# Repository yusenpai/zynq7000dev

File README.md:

# Zynq 7000 SoC Dev Board

Đây là một board PCB 6 lớp thiết kế quanh con chip XC7Z010-1CLG400C, thuộc họ SoC Zynq 7000 của AMD. Con chip có một nửa là (2) lõi CPU (ARM Cortex-A9) + một đống ngoại vi (UART, I2C, SPI, USB,...); nửa còn lại là FPGA. Rất phù hợp cho những ứng dụng kết hợp Hardware + Software.

Thường thì những board FPGA (đặc biệt là thể loại SoC thế này) rất mắc tiền. Xem [https://www.amd.com/en/products/adaptive-socs-and-fpgas/evaluation-boards/ek-z7-zc702-g.html]. Trong khi đó, mạch in khá là rẻ, chip thì mình cũng kiếm được trên Aliexpress (với đi freesample), nên mình quyết định làm một board thế này.

Schematic, PCB vẫn đang trong quá trình phát triển và có thể sai sót. Mình sẽ cập nhật thêm nếu mạch chạy được 😂.

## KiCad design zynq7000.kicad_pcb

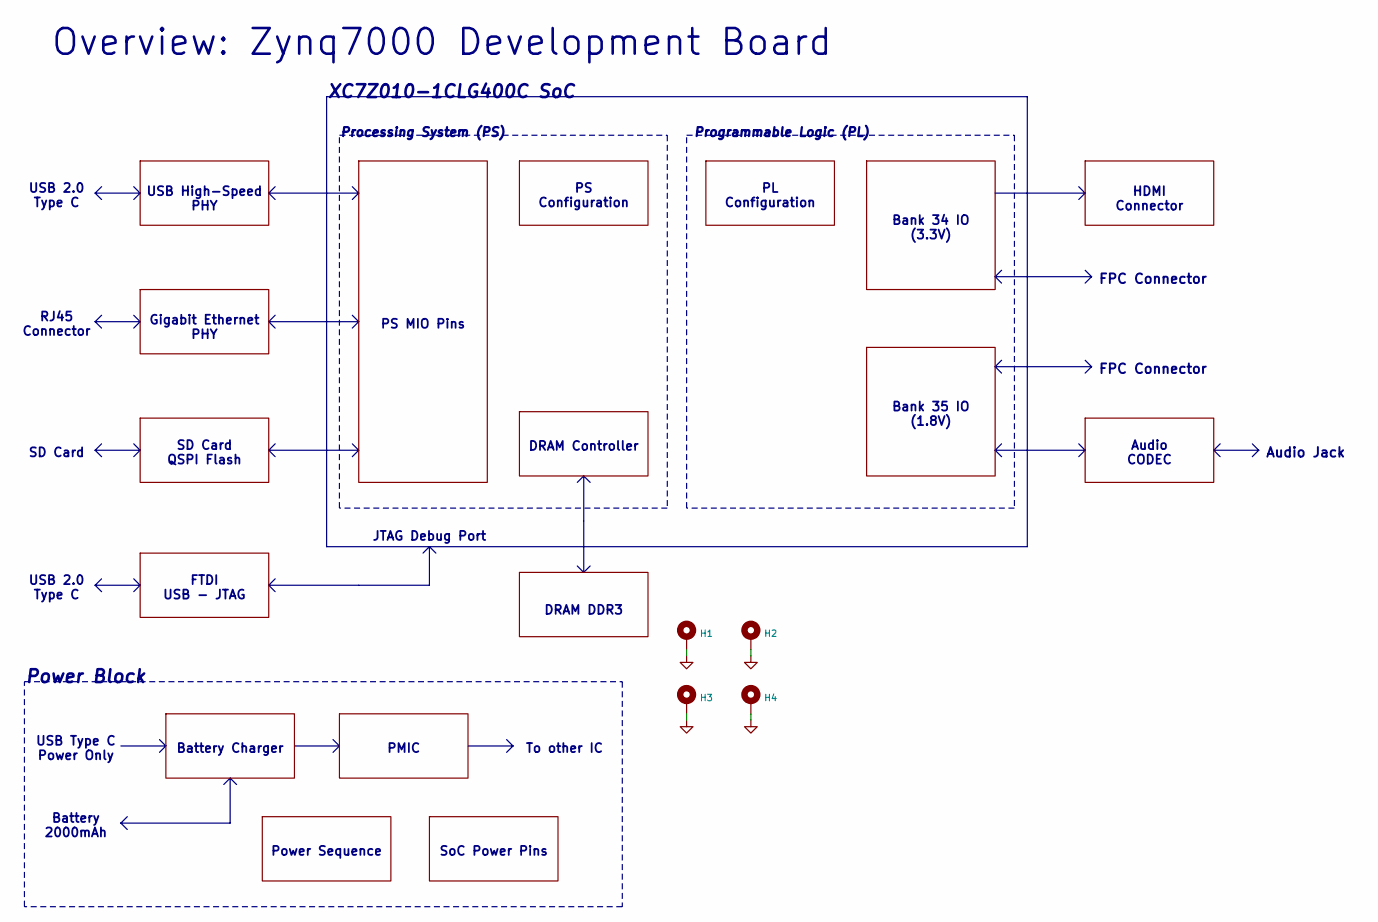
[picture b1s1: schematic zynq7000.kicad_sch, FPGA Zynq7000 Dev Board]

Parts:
H1, H2, H3, H4: MountingHole_Pad; MountingHole_3mm_Pad_Via

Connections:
GND: H1.1, H2.1, H3.1, H4.1; also elsewhere on the board

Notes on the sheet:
USB 2.0 Type C
Bank 34 IO (3.3V)
Processing System (PS)
FPC Connector
FTDI USB - JTAG
Audio Jack
PS Configuration
DRAM DDR3
Programmable Logic (PL)
Overview: Zynq7000 Development Board
To other IC
JTAG Debug Port
Power Block
SoC Power Pins
RJ45 Connector
USB Type C Power Only
PS MIO Pins
USB High-Speed PHY
Battery Charger
Gigabit Ethernet PHY
Power Sequence
HDMI Connector
Battery 2000mAh
PMIC
Audio CODEC
SD Card QSPI Flash
PL Configuration
Bank 35 IO (1.8V)
XC7Z010-1CLG400C SoC
DRAM Controller
SD Card

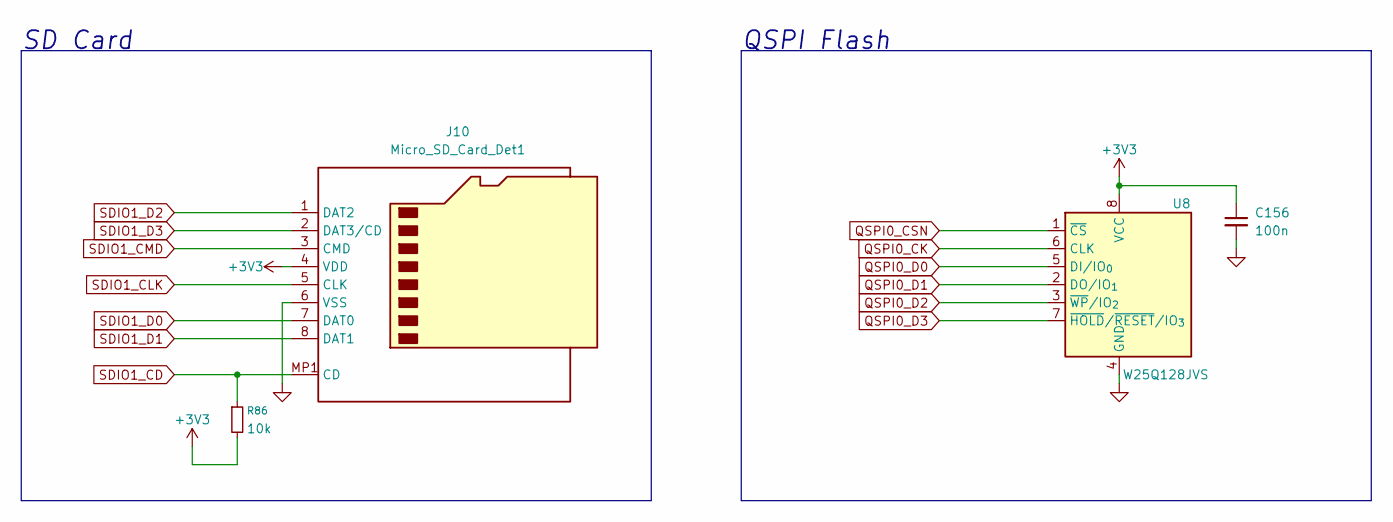
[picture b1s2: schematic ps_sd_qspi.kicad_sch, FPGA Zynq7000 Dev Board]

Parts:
C156: 100n; C_0402_1005Metric
J10: Micro_SD_Card_Det1; 5008730806
R86: 10k; R_0402_1005Metric
U8: W25Q128JVS; SOIC-8_5.3x5.3mm_P1.27mm

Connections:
+3V3: C156.1, J10.4 (VDD), R86.2, U8.8 (VCC); also elsewhere on the board
GND: C156.2, J10.6 (VSS), U8.4 (GND); also elsewhere on the board
QSPI0_CK: U8.6 (CLK); also elsewhere on the board
QSPI0_CSN: U8.1 (~CS); also elsewhere on the board
QSPI0_D0: U8.5 (DI/IO_{0}); also elsewhere on the board
QSPI0_D1: U8.2 (DO/IO_{1}); also elsewhere on the board
QSPI0_D2: U8.3 (~WP/IO_{2}); also elsewhere on the board
QSPI0_D3: U8.7 (~HOLD/~RESET/IO_{3}); also elsewhere on the board
SDIO1_CD: J10.MP1 (CD), R86.1; also elsewhere on the board
SDIO1_CLK: J10.5 (CLK); also elsewhere on the board
SDIO1_CMD: J10.3 (CMD); also elsewhere on the board
SDIO1_D0: J10.7 (DAT0); also elsewhere on the board
SDIO1_D1: J10.8 (DAT1); also elsewhere on the board
SDIO1_D2: J10.1 (DAT2); also elsewhere on the board
SDIO1_D3: J10.2 (DAT3/CD); also elsewhere on the board

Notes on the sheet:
QSPI Flash
SD Card

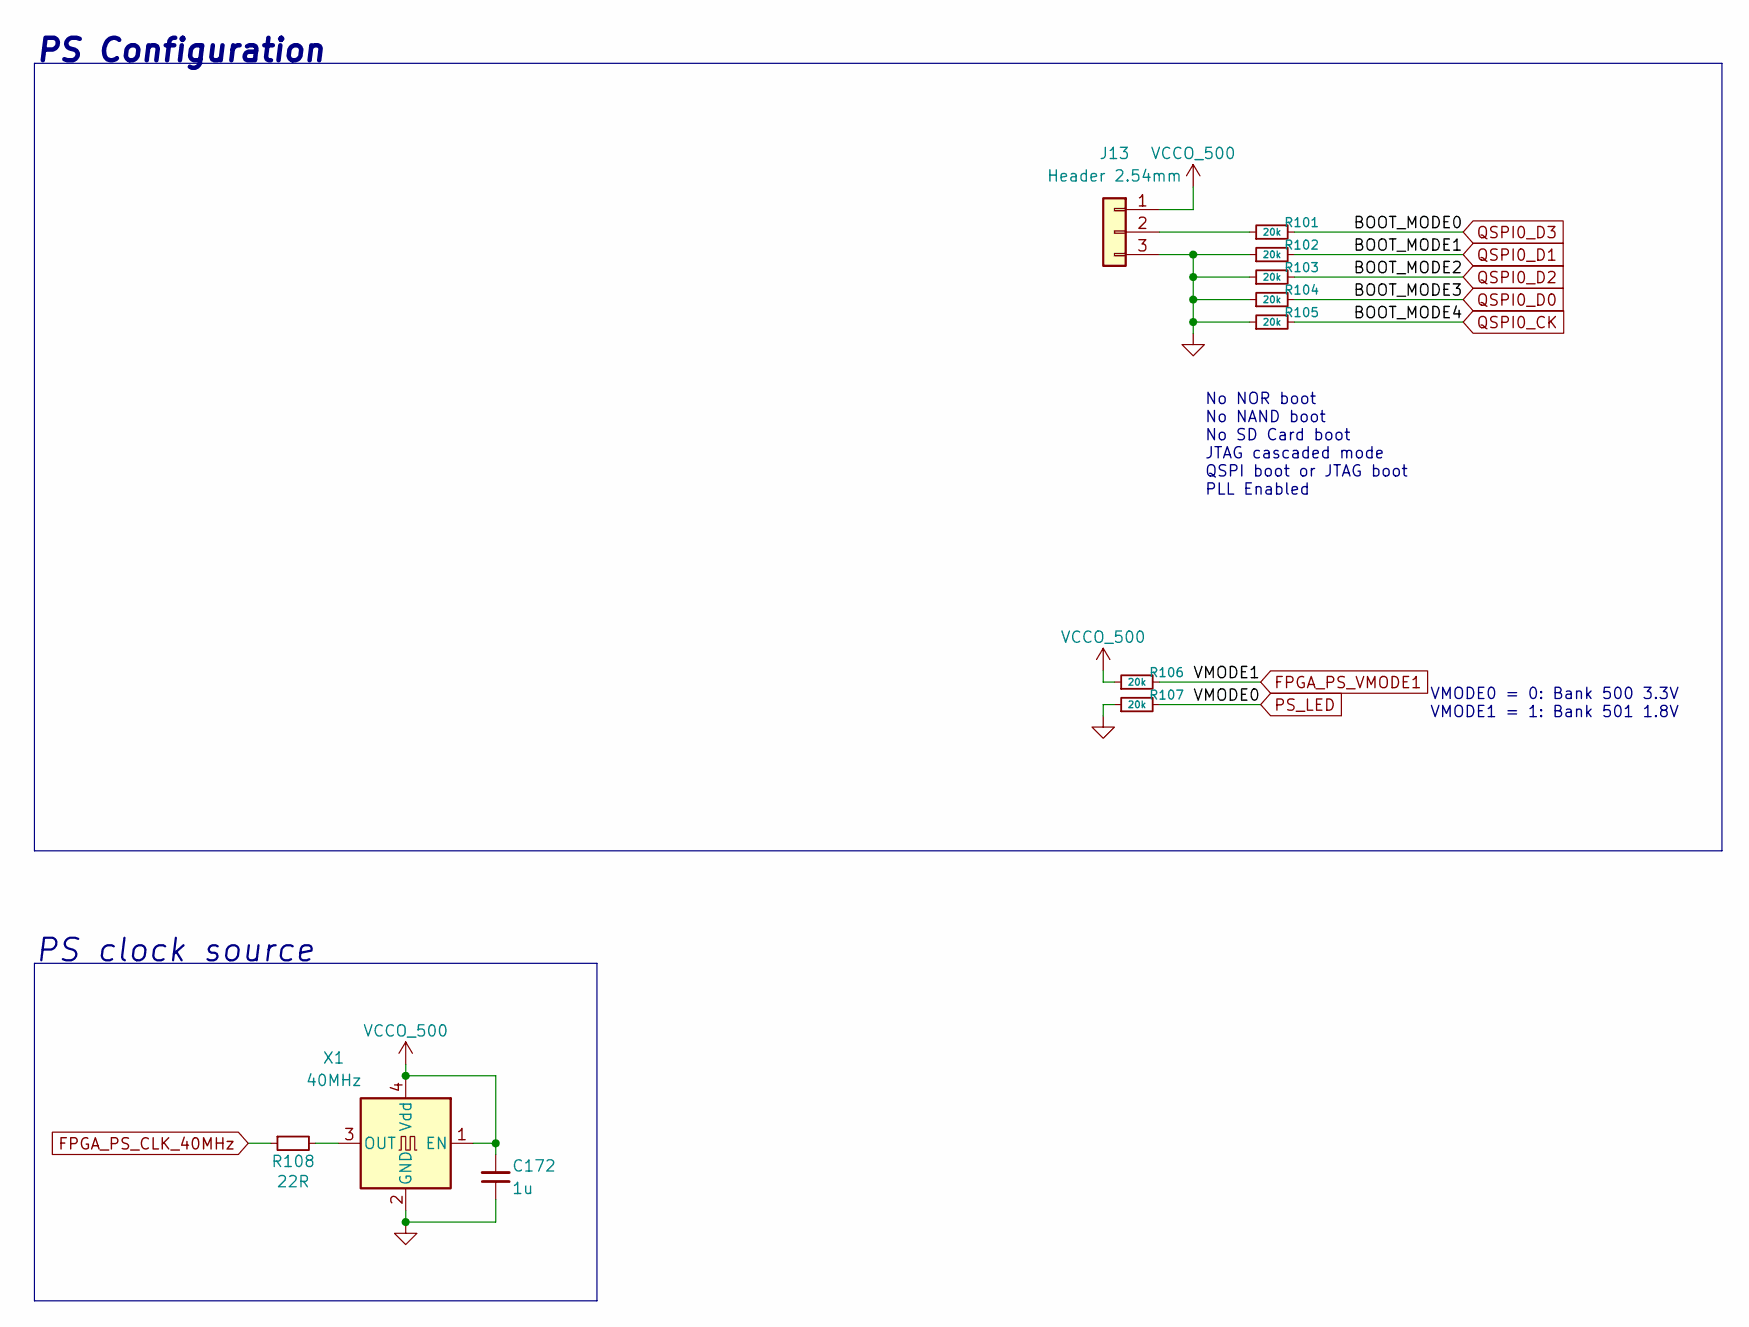
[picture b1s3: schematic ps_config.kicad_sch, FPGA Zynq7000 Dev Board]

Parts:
C172: 1u; C_0402_1005Metric
J13: Header 2.54mm; PinHeader_1x03_P2.54mm_Vertical
R101, R102, R103, R104, R105, R106, R107: 20k; R_0402_1005Metric
R108: 22R; R_0402_1005Metric
X1: 40MHz; Oscillator_SMD_Abracon_ASE-4Pin_3.2x2.5mm

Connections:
+3V3: C172.2, J13.1, R106.1, X1.1 (EN), X1.4 (Vdd); also elsewhere on the board
FPGA_PS_CLK_40MHz: R108.1; also elsewhere on the board
FPGA_PS_VMODE1: R106.2; also elsewhere on the board
GND: C172.1, J13.3, R102.1, R103.1, R104.1, R105.1, R107.1, X1.2 (GND); also elsewhere on the board
unnamed: J13.2, R101.1
unnamed: R108.2, X1.3 (OUT)
PS_LED: R107.2; also elsewhere on the board
QSPI0_CK: R105.2; also elsewhere on the board
QSPI0_D0: R104.2; also elsewhere on the board
QSPI0_D1: R102.2; also elsewhere on the board
QSPI0_D2: R103.2; also elsewhere on the board
QSPI0_D3: R101.2; also elsewhere on the board

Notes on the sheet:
PS clock source
VMODE0 = 0: Bank 500 3.3V VMODE1 = 1: Bank 501 1.8V
PS Configuration
No NOR boot No NAND boot No SD Card boot JTAG cascaded mode QSPI boot or JTAG boot PLL Enabled

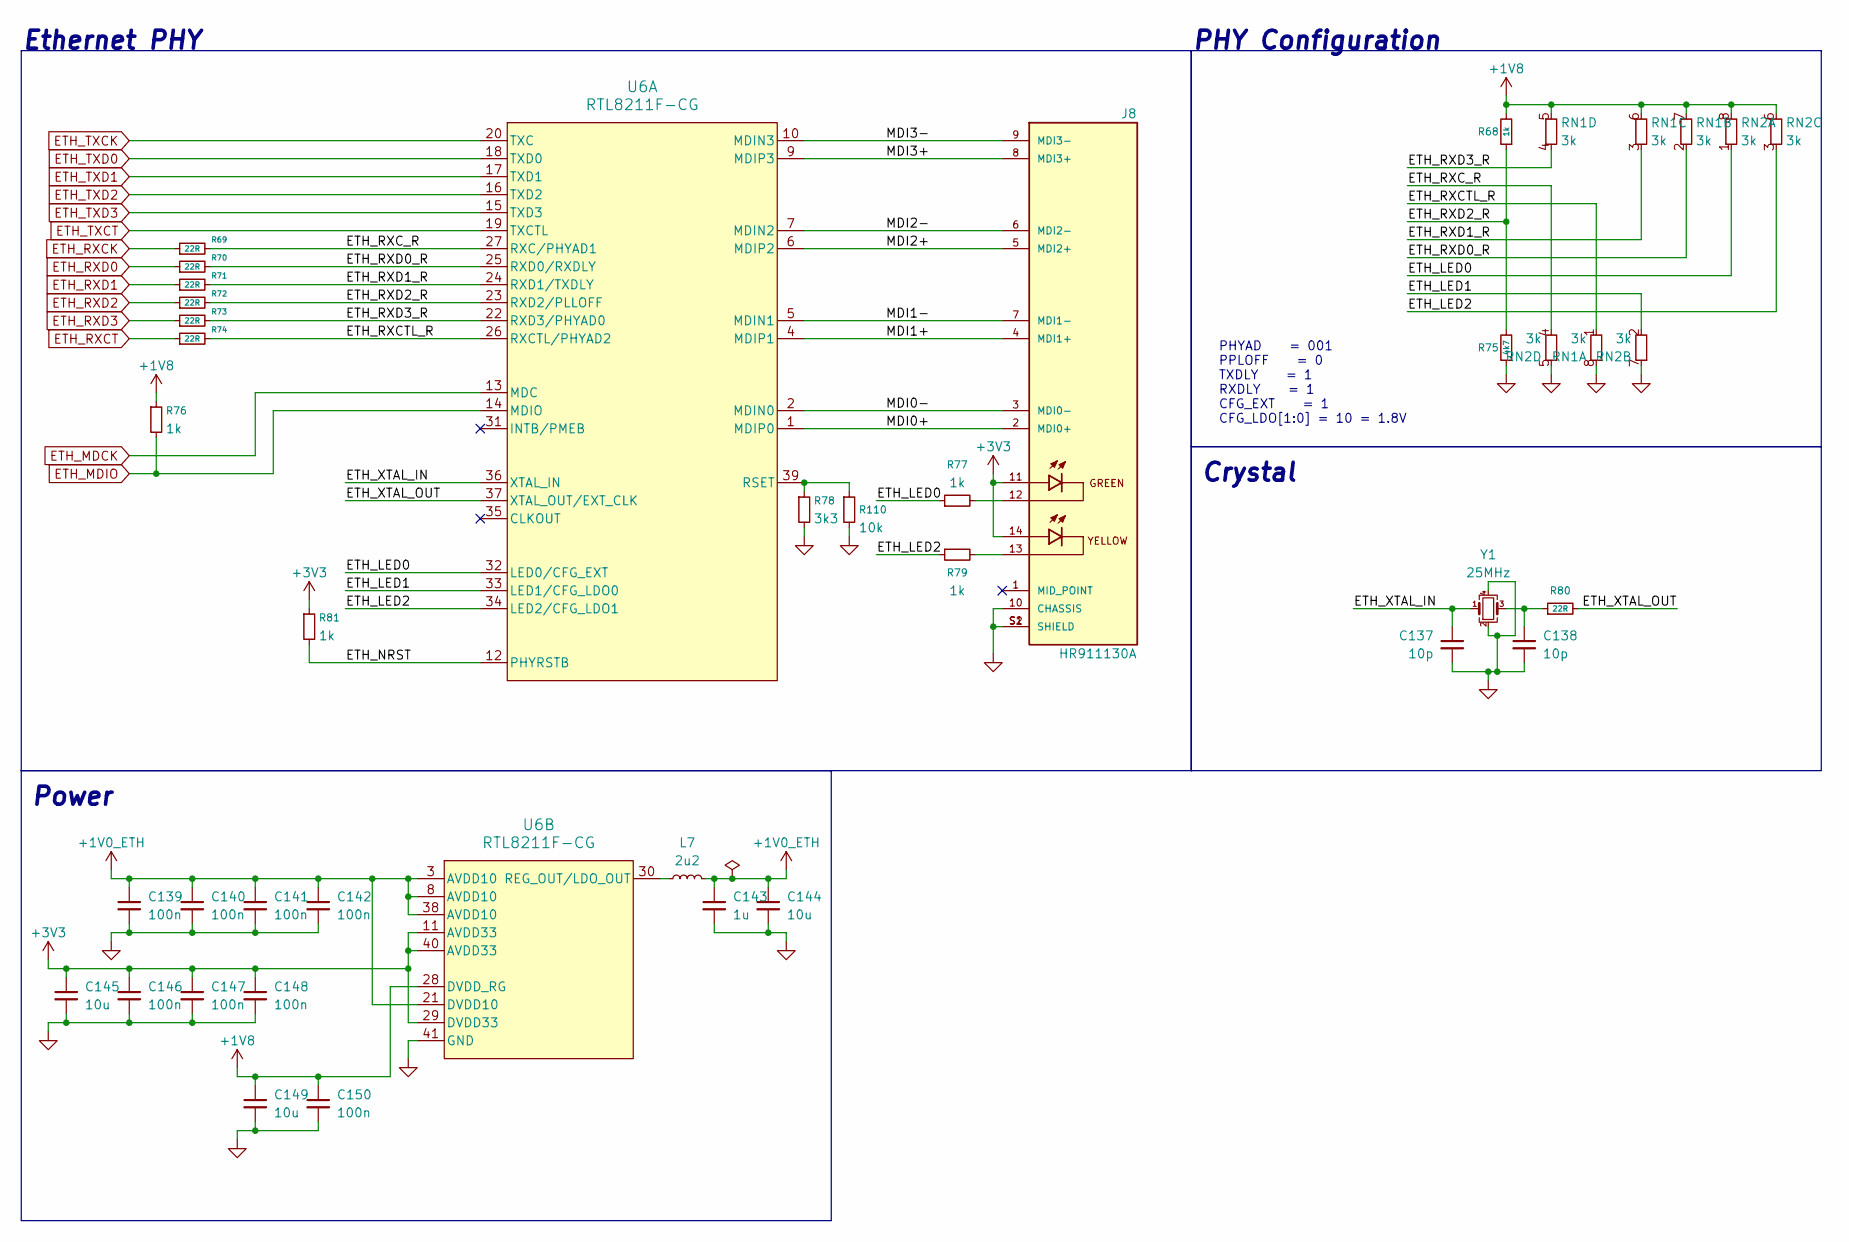
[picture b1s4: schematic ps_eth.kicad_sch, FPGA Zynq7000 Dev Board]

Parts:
C137, C138: 10p; C_0402_1005Metric
C139, C140, C141, C142, C146, C147, C148, C150: 100n; C_0402_1005Metric
C143: 1u; C_0402_1005Metric
C144, C145, C149: 10u; C_0402_1005Metric
J8: HR911130A; HANRUN_HR911130A; PARTREV A
L7: 2u2; L_1008_2520Metric
R68, R76, R77, R79, R81: 1k; R_0402_1005Metric
R69, R70, R71, R72, R73, R74, R80: 22R; R_0402_1005Metric
R75: 4k7; R_0402_1005Metric
R78: 3k3; R_0402_1005Metric
R110: 10k; R_0402_1005Metric
RN1, RN2: 3k; R_Array_Concave_4x0402
U6: RTL8211F-CG; QFN_40_7x7mm_RTL8211F
Y1: 25MHz; Crystal_SMD_3225-4Pin_3.2x2.5mm

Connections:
+1V0_ETH: C139.1, C140.1, C141.1, C142.1, C143.1, C144.1, L7.2, U6.3 (AVDD10), U6.8 (AVDD10), U6.21 (DVDD10), U6.38 (AVDD10)
+1V8: C149.1, C150.1, R68.2, R76.1, RN1.5 (R4.2), RN1.6 (R3.2), RN1.7 (R2.2), RN2.6 (R3.2), RN2.8, U6.28 (DVDD_RG); also elsewhere on the board
+3V3: C145.1, C146.1, C147.1, C148.1, J8.11, J8.14, R81.1, U6.11 (AVDD33), U6.29 (DVDD33), U6.40 (AVDD33); also elsewhere on the board
/Gigabit Ethernet PHY/ETH_LED0: R77.1, RN2.1, U6.32 (LED0/CFG_EXT)
/Gigabit Ethernet PHY/ETH_LED1: RN2.2 (R2.1), U6.33 (LED1/CFG_LDO0)
/Gigabit Ethernet PHY/ETH_LED2: R79.1, RN2.3 (R3.1), U6.34 (LED2/CFG_LDO1)
/Gigabit Ethernet PHY/ETH_NRST: R81.2, U6.12 (PHYRSTB)
/Gigabit Ethernet PHY/ETH_RXCTL_R: R74.2, RN1.1, U6.26 (RXCTL/PHYAD2)
/Gigabit Ethernet PHY/ETH_RXC_R: R69.2, RN2.4 (R4.1), U6.27 (RXC/PHYAD1)
/Gigabit Ethernet PHY/ETH_RXD0_R: R70.2, RN1.2 (R2.1), U6.25 (RXD0/RXDLY)
/Gigabit Ethernet PHY/ETH_RXD1_R: R71.2, RN1.3 (R3.1), U6.24 (RXD1/TXDLY)
/Gigabit Ethernet PHY/ETH_RXD2_R: R68.1, R72.2, R75.2, U6.23 (RXD2/PLLOFF)
/Gigabit Ethernet PHY/ETH_RXD3_R: R73.2, RN1.4 (R4.1), U6.22 (RXD3/PHYAD0)
/Gigabit Ethernet PHY/ETH_XTAL_IN: C137.1, U6.36 (XTAL_IN), Y1.1
/Gigabit Ethernet PHY/ETH_XTAL_OUT: R80.2, U6.37 (XTAL_OUT/EXT_CLK)
/Gigabit Ethernet PHY/MDI0+: J8.2 (MDI0+), U6.1 (MDIP0)
/Gigabit Ethernet PHY/MDI0-: J8.3 (MDI0-), U6.2 (MDIN0)
/Gigabit Ethernet PHY/MDI1+: J8.4 (MDI1+), U6.4 (MDIP1)
/Gigabit Ethernet PHY/MDI1-: J8.7 (MDI1-), U6.5 (MDIN1)
/Gigabit Ethernet PHY/MDI2+: J8.5 (MDI2+), U6.6 (MDIP2)
/Gigabit Ethernet PHY/MDI2-: J8.6 (MDI2-), U6.7 (MDIN2)
/Gigabit Ethernet PHY/MDI3+: J8.8 (MDI3+), U6.9 (MDIP3)
/Gigabit Ethernet PHY/MDI3-: J8.9 (MDI3-), U6.10 (MDIN3)
ETH_MDCK: U6.13 (MDC); also elsewhere on the board
ETH_MDIO: R76.2, U6.14 (MDIO); also elsewhere on the board
ETH_RXCK: R69.1; also elsewhere on the board
ETH_RXCT: R74.1; also elsewhere on the board
ETH_RXD0: R70.1; also elsewhere on the board
ETH_RXD1: R71.1; also elsewhere on the board
ETH_RXD2: R72.1; also elsewhere on the board
ETH_RXD3: R73.1; also elsewhere on the board
ETH_TXCK: U6.20 (TXC); also elsewhere on the board
ETH_TXCT: U6.19 (TXCTL); also elsewhere on the board
ETH_TXD0: U6.18 (TXD0); also elsewhere on the board
ETH_TXD1: U6.17 (TXD1); also elsewhere on the board
ETH_TXD2: U6.16 (TXD2); also elsewhere on the board
ETH_TXD3: U6.15 (TXD3); also elsewhere on the board
GND: C137.2, C138.2, C139.2, C140.2, C141.2, C142.2, C143.2, C144.2, C145.2, C146.2, C147.2, C148.2, C149.2, C150.2, J8.10 (CHASSIS), J8.S1 (SHIELD), J8.S2 (SHIELD), R75.1, R78.2, R110.2, RN1.8, RN2.5 (R4.2), RN2.7 (R2.2), U6.41 (GND), Y1.2, Y1.4; also elsewhere on the board
unnamed: C138.1, R80.1, Y1.3
unnamed: J8.12, R77.2
unnamed: J8.13, R79.2
unnamed: R78.1, R110.1, U6.39 (RSET)
unnamed: L7.1, U6.30 (REG_OUT/LDO_OUT)

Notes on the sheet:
Ethernet PHY
Crystal
PHY Configuration
Power
PHYAD = 001 PPLOFF = 0 TXDLY = 1 RXDLY = 1 CFG_EXT = 1 CFG_LDO[1:0] = 10 = 1.8V

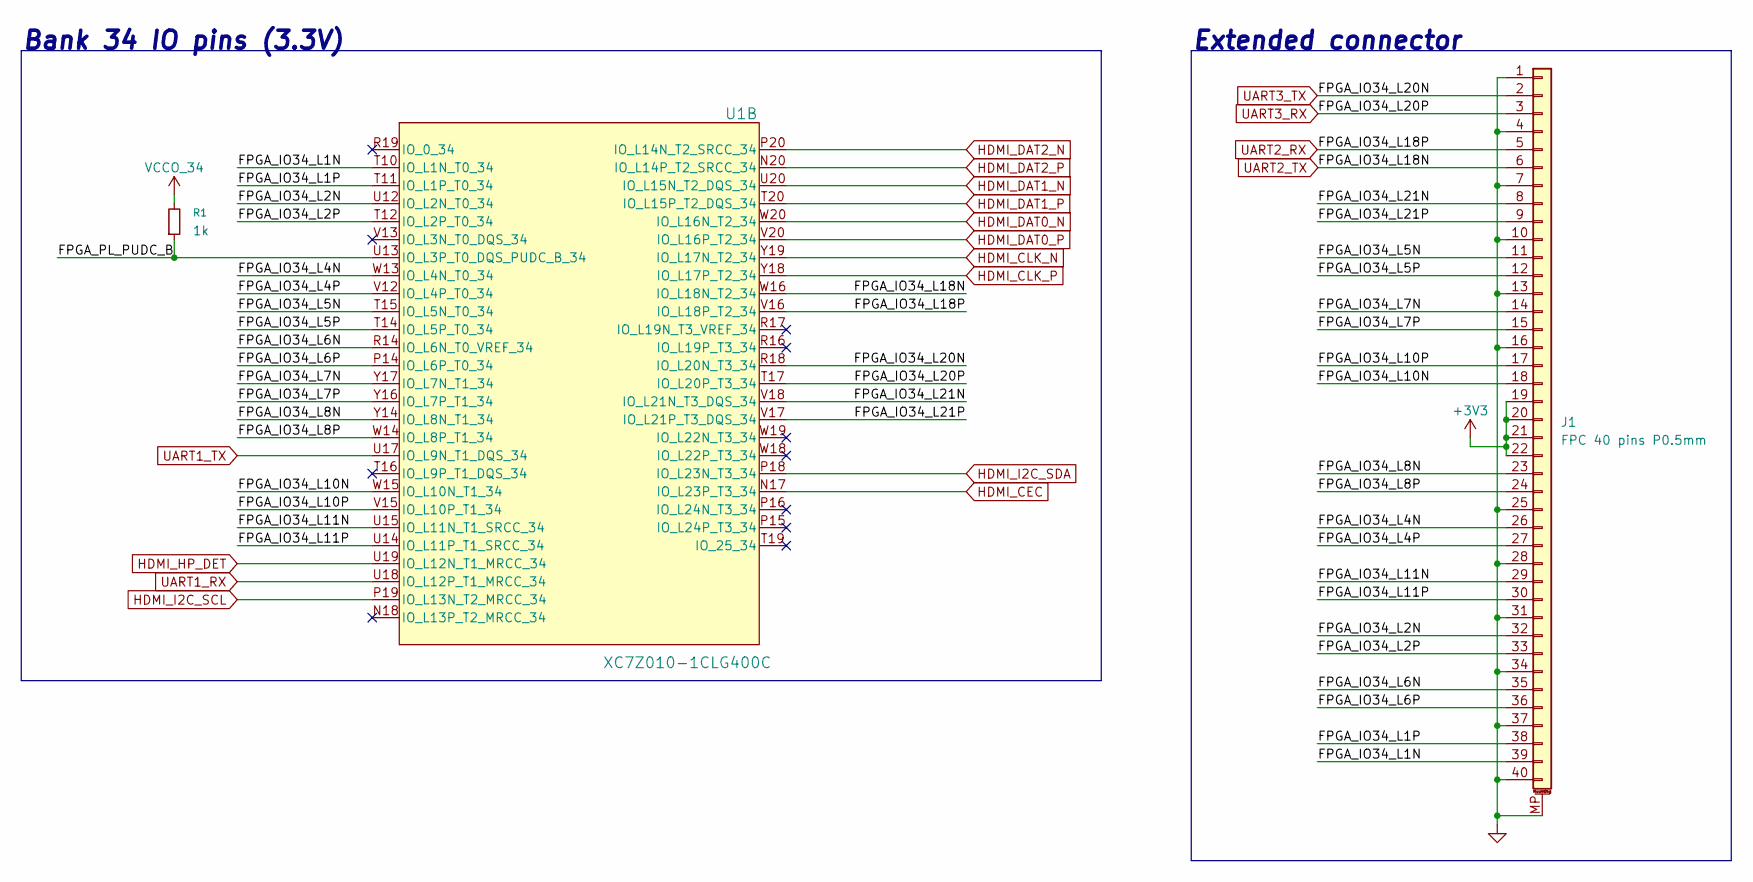
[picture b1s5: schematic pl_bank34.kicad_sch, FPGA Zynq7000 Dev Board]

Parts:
J1: FPC 40 pins P0.5mm; Amphenol_F32Q-1A7x1-11040_1x40-1MP_P0.5mm_Horizontal
R1: 1k; R_0402_1005Metric
U1: XC7Z010-1CLG400C; CLG400_XIL-L

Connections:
+3V3: J1.19, J1.20, J1.21, J1.22, R1.2; also elsewhere on the board
/Bank 34 (3.3V)/FPGA_IO34_L1N: J1.39, U1.T10 (IO_L1N_T0_34)
/Bank 34 (3.3V)/FPGA_IO34_L1P: J1.38, U1.T11 (IO_L1P_T0_34)
/Bank 34 (3.3V)/FPGA_IO34_L2N: J1.32, U1.U12 (IO_L2N_T0_34)
/Bank 34 (3.3V)/FPGA_IO34_L2P: J1.33, U1.T12 (IO_L2P_T0_34)
/Bank 34 (3.3V)/FPGA_IO34_L4N: J1.26, U1.W13 (IO_L4N_T0_34)
/Bank 34 (3.3V)/FPGA_IO34_L4P: J1.27, U1.V12 (IO_L4P_T0_34)
/Bank 34 (3.3V)/FPGA_IO34_L5N: J1.11, U1.T15 (IO_L5N_T0_34)
/Bank 34 (3.3V)/FPGA_IO34_L5P: J1.12, U1.T14 (IO_L5P_T0_34)
/Bank 34 (3.3V)/FPGA_IO34_L6N: J1.35, U1.R14 (IO_L6N_T0_VREF_34)
/Bank 34 (3.3V)/FPGA_IO34_L6P: J1.36, U1.P14 (IO_L6P_T0_34)
/Bank 34 (3.3V)/FPGA_IO34_L7N: J1.14, U1.Y17 (IO_L7N_T1_34)
/Bank 34 (3.3V)/FPGA_IO34_L7P: J1.15, U1.Y16 (IO_L7P_T1_34)
/Bank 34 (3.3V)/FPGA_IO34_L8N: J1.23, U1.Y14 (IO_L8N_T1_34)
/Bank 34 (3.3V)/FPGA_IO34_L8P: J1.24, U1.W14 (IO_L8P_T1_34)
/Bank 34 (3.3V)/FPGA_IO34_L10N: J1.18, U1.W15 (IO_L10N_T1_34)
/Bank 34 (3.3V)/FPGA_IO34_L10P: J1.17, U1.V15 (IO_L10P_T1_34)
/Bank 34 (3.3V)/FPGA_IO34_L11N: J1.29, U1.U15 (IO_L11N_T1_SRCC_34)
/Bank 34 (3.3V)/FPGA_IO34_L11P: J1.30, U1.U14 (IO_L11P_T1_SRCC_34)
/Bank 34 (3.3V)/FPGA_IO34_L21N: J1.8, U1.V18 (IO_L21N_T3_DQS_34)
/Bank 34 (3.3V)/FPGA_IO34_L21P: J1.9, U1.V17 (IO_L21P_T3_DQS_34)
/Bank 34 (3.3V)/FPGA_PL_PUDC_B: R1.1, U1.U13 (IO_L3P_T0_DQS_PUDC_B_34)
GND: J1.1, J1.4, J1.7, J1.10, J1.13, J1.16, J1.25, J1.28, J1.31, J1.34, J1.37, J1.40, J1.MP (MountPin); also elsewhere on the board
HDMI_CEC: U1.N17 (IO_L23P_T3_34); also elsewhere on the board
HDMI_CLK_N: U1.Y19 (IO_L17N_T2_34); also elsewhere on the board
HDMI_CLK_P: U1.Y18 (IO_L17P_T2_34); also elsewhere on the board
HDMI_DAT0_N: U1.W20 (IO_L16N_T2_34); also elsewhere on the board
HDMI_DAT0_P: U1.V20 (IO_L16P_T2_34); also elsewhere on the board
HDMI_DAT1_N: U1.U20 (IO_L15N_T2_DQS_34); also elsewhere on the board
HDMI_DAT1_P: U1.T20 (IO_L15P_T2_DQS_34); also elsewhere on the board
HDMI_DAT2_N: U1.P20 (IO_L14N_T2_SRCC_34); also elsewhere on the board
HDMI_DAT2_P: U1.N20 (IO_L14P_T2_SRCC_34); also elsewhere on the board
HDMI_HP_DET: U1.U19 (IO_L12N_T1_MRCC_34); also elsewhere on the board
HDMI_I2C_SCL: U1.P19 (IO_L13N_T2_MRCC_34); also elsewhere on the board
HDMI_I2C_SDA: U1.P18 (IO_L23N_T3_34); also elsewhere on the board
UART1_RX: U1.U18 (IO_L12P_T1_MRCC_34); also elsewhere on the board
UART1_TX: U1.U17 (IO_L9N_T1_DQS_34); also elsewhere on the board
UART2_RX: J1.5, U1.V16 (IO_L18P_T2_34); also elsewhere on the board
UART2_TX: J1.6, U1.W16 (IO_L18N_T2_34); also elsewhere on the board
UART3_RX: J1.3, U1.T17 (IO_L20P_T3_34); also elsewhere on the board
UART3_TX: J1.2, U1.R18 (IO_L20N_T3_34); also elsewhere on the board

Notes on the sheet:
Bank 34 IO pins (3.3V)
Extended connector

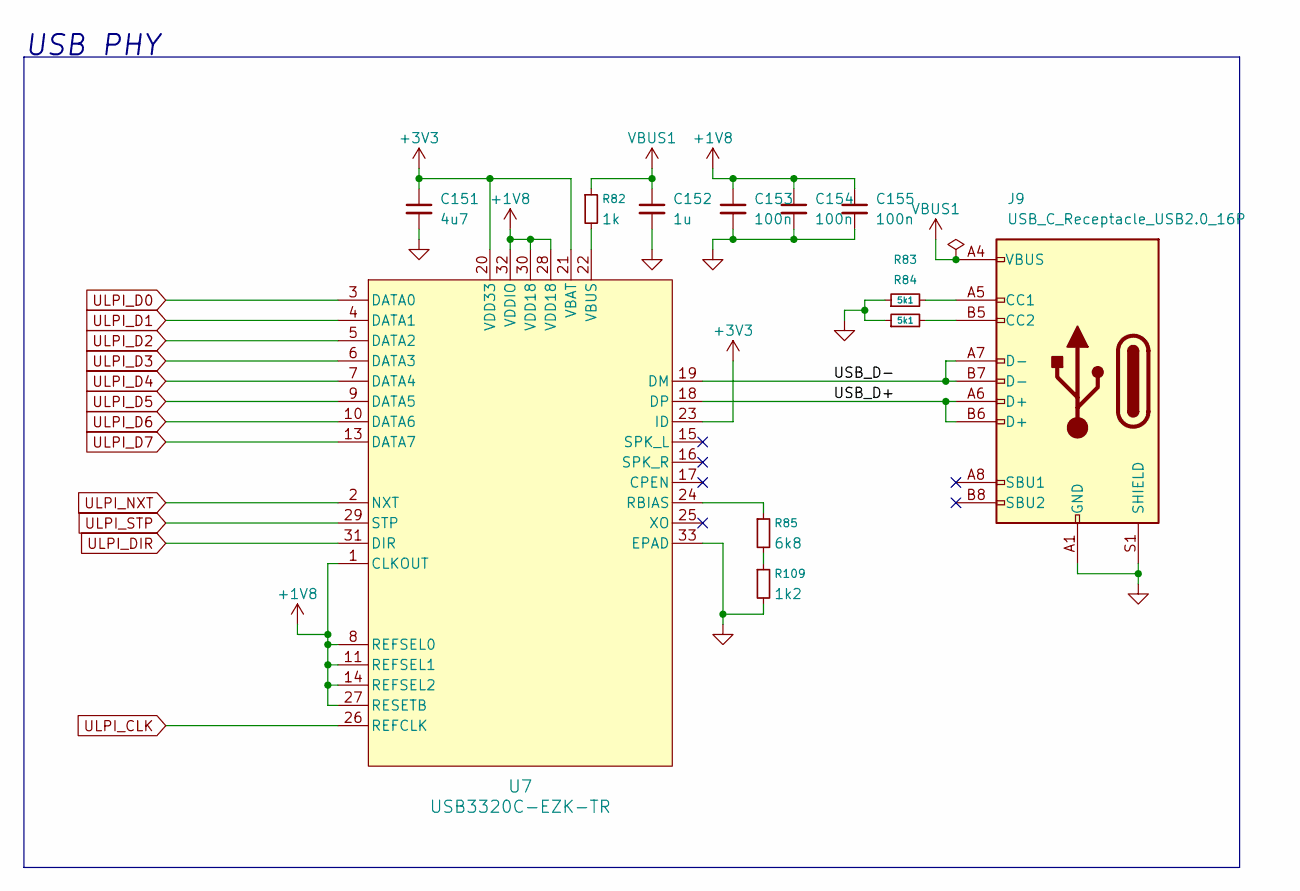
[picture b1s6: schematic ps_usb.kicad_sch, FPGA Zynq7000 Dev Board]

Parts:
C151: 4u7; C_0402_1005Metric
C152: 1u; C_0402_1005Metric
C153, C154, C155: 100n; C_0402_1005Metric
J9: USB_C_Receptacle_USB2.0_16P; USB_C_Receptacle_GCT_USB4105-xx-A_16P_TopMnt_Horizontal
R82: 1k; R_0402_1005Metric
R83, R84: 5k1; R_0402_1005Metric
R85: 6k8; R_0402_1005Metric
R109: 1k2; R_0402_1005Metric
U7: USB3320C-EZK-TR; QFN32_5X5_USB3320

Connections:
+1V8: C153.1, C154.1, C155.1, U7.1 (CLKOUT), U7.8 (REFSEL0), U7.11 (REFSEL1), U7.14 (REFSEL2), U7.27 (RESETB), U7.28 (VDD18), U7.30 (VDD18), U7.32 (VDDIO); also elsewhere on the board
+3V3: C151.1, U7.20 (VDD33), U7.21 (VBAT), U7.23 (ID); also elsewhere on the board
/USB HS PHY/USB_D+: J9.A6 (D+), J9.B6 (D+), U7.18 (DP)
/USB HS PHY/USB_D-: J9.A7 (D-), J9.B7 (D-), U7.19 (DM)
GND: C151.2, C152.2, C153.2, C154.2, C155.2, J9.A1 (GND), J9.A12 (GND), J9.B1 (GND), J9.B12 (GND), J9.S1 (SHIELD), R83.1, R84.1, R109.2, U7.33 (EPAD); also elsewhere on the board
unnamed: J9.A5 (CC1), R83.2
unnamed: J9.B5 (CC2), R84.2
unnamed: R85.2, R109.1
unnamed: R85.1, U7.24 (RBIAS)
unnamed: R82.2, U7.22 (VBUS)
ULPI_CLK: U7.26 (REFCLK); also elsewhere on the board
ULPI_D0: U7.3 (DATA0); also elsewhere on the board
ULPI_D1: U7.4 (DATA1); also elsewhere on the board
ULPI_D2: U7.5 (DATA2); also elsewhere on the board
ULPI_D3: U7.6 (DATA3); also elsewhere on the board
ULPI_D4: U7.7 (DATA4); also elsewhere on the board
ULPI_D5: U7.9 (DATA5); also elsewhere on the board
ULPI_D6: U7.10 (DATA6); also elsewhere on the board
ULPI_D7: U7.13 (DATA7); also elsewhere on the board
ULPI_DIR: U7.31 (DIR); also elsewhere on the board
ULPI_NXT: U7.2 (NXT); also elsewhere on the board
ULPI_STP: U7.29 (STP); also elsewhere on the board
VBUS1: C152.1, J9.A4 (VBUS), J9.A9 (VBUS), J9.B4 (VBUS), J9.B9 (VBUS), R82.1; also elsewhere on the board

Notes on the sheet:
USB PHY

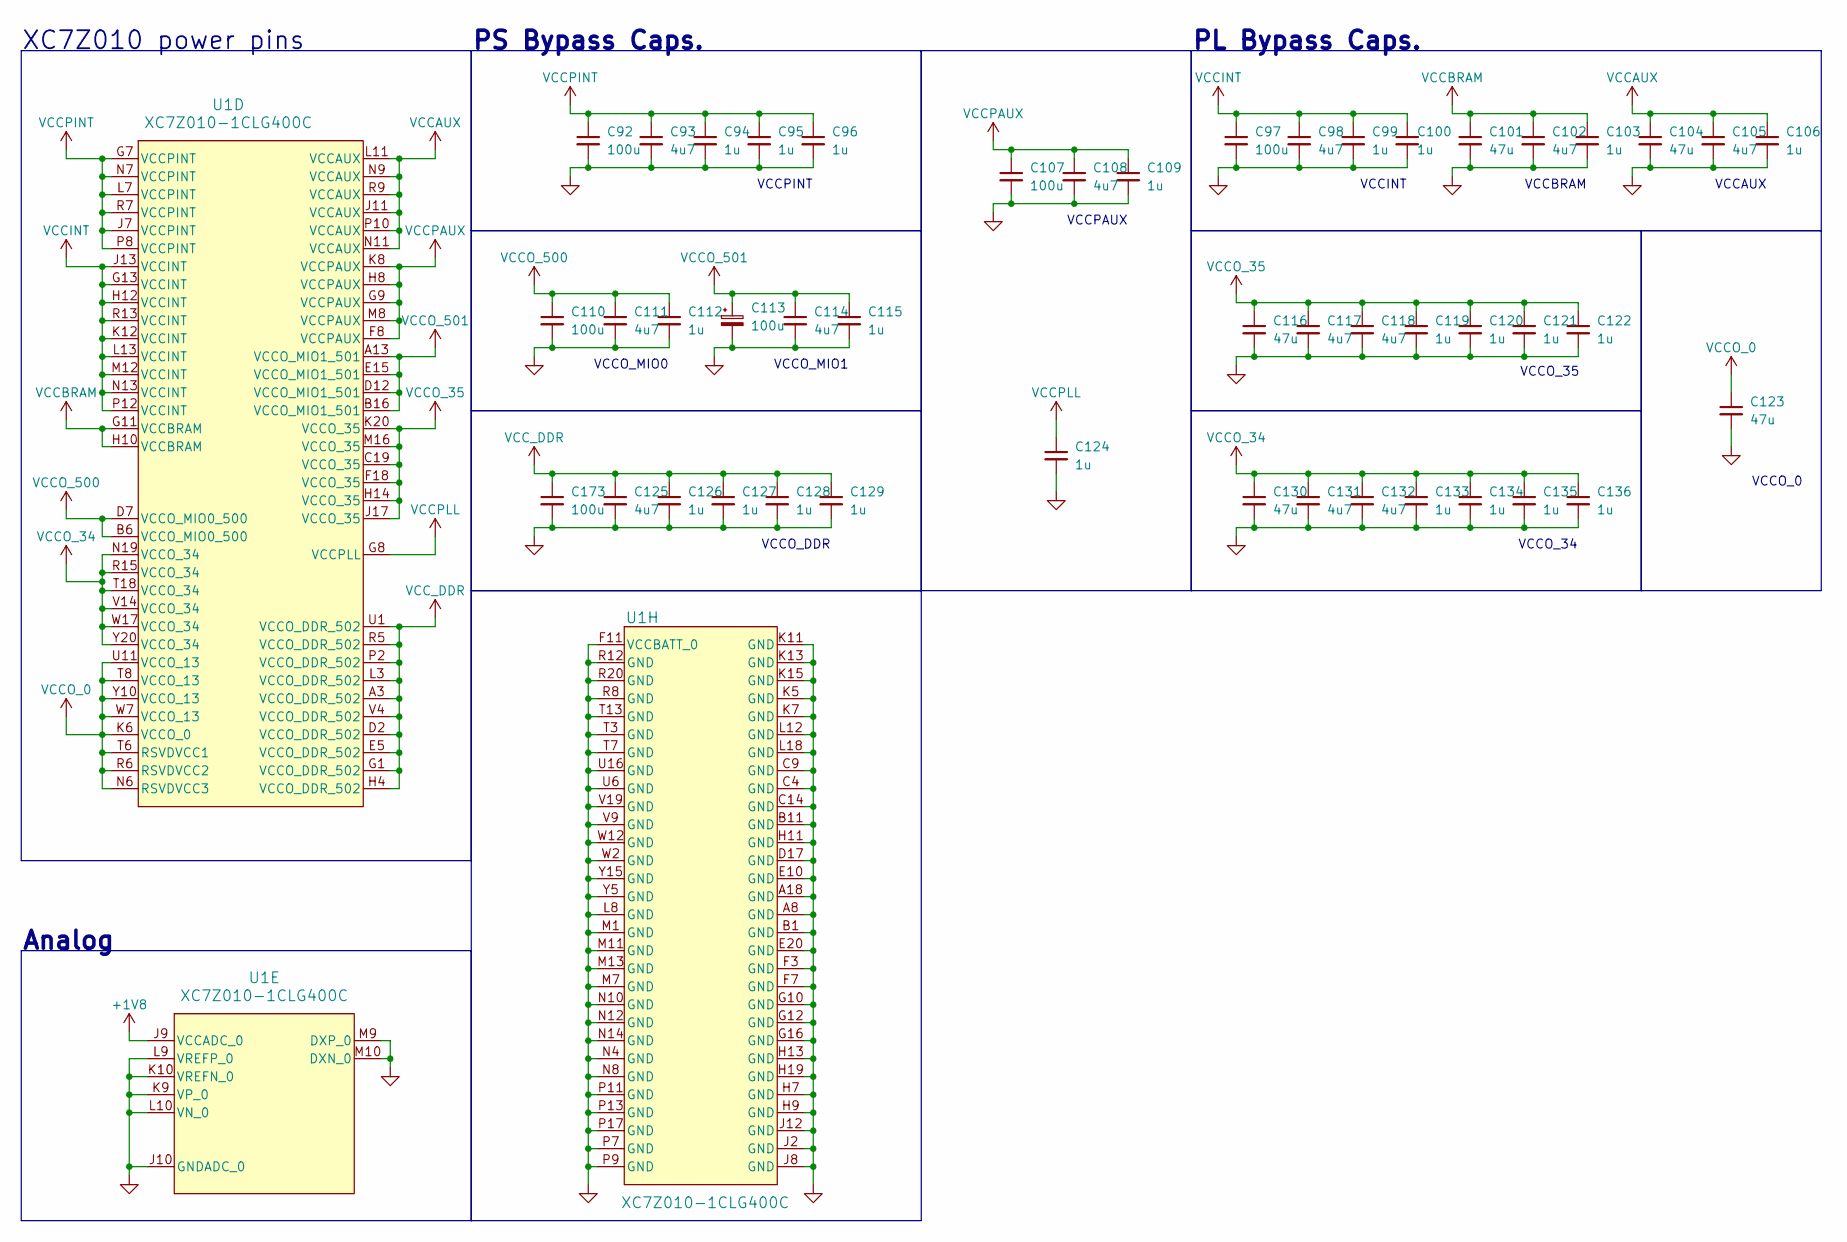
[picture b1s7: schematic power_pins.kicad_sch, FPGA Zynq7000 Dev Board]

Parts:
C92, C97, C107, C110, C113, C173: 100u; C_1206_3216Metric
C93, C98, C102, C105, C108, C111, C114, C117, C118, C125, C131, C132: 4u7; C_0402_1005Metric
C94, C95, C96, C99, C100, C103, C106, C109, C112, C115, C119, C120, C121, C122, C124, C126, C127, C128, C129, C133, C134, C135, C136: 1u; C_0402_1005Metric
C101, C104, C116, C123, C130: 47u; C_1206_3216Metric
U1: XC7Z010-1CLG400C; CLG400_XIL-L

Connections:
+1V0: C92.1, C93.1, C94.1, C95.1, C96.1, C97.1, C98.1, C99.1, C100.1, C101.1, C102.1, C103.1, U1.G7 (VCCPINT), U1.G11 (VCCBRAM), U1.G13 (VCCINT), U1.H10 (VCCBRAM), U1.H12 (VCCINT), U1.J7 (VCCPINT), U1.J13 (VCCINT), U1.K12 (VCCINT), U1.L7 (VCCPINT), U1.L13 (VCCINT), U1.M12 (VCCINT), U1.N7 (VCCPINT), U1.N13 (VCCINT), U1.P8 (VCCPINT), U1.P12 (VCCINT), U1.R7 (VCCPINT), U1.R13 (VCCINT); also elsewhere on the board
+1V8: C104.1, C105.1, C106.1, C107.1, C108.1, C109.1, C113.1, C114.1, C115.1, C116.1, C117.1, C118.1, C119.1, C120.1, C121.1, C122.1, C124.1, U1.A13 (VCCO_MIO1_501), U1.B16 (VCCO_MIO1_501), U1.C19 (VCCO_35), U1.D12 (VCCO_MIO1_501), U1.E15 (VCCO_MIO1_501), U1.F8 (VCCPAUX), U1.F18 (VCCO_35), U1.G8 (VCCPLL), U1.G9 (VCCPAUX), U1.H8 (VCCPAUX), U1.H14 (VCCO_35), U1.J9 (VCCADC_0), U1.J11 (VCCAUX), U1.J17 (VCCO_35), U1.K8 (VCCPAUX), U1.K20 (VCCO_35), U1.L11 (VCCAUX), U1.M8 (VCCPAUX), U1.M16 (VCCO_35), U1.N9 (VCCAUX), U1.N11 (VCCAUX), U1.P10 (VCCAUX), U1.R9 (VCCAUX); also elsewhere on the board
+1V35: C125.1, C126.1, C127.1, C128.1, C129.1, C173.1, U1.A3 (VCCO_DDR_502), U1.D2 (VCCO_DDR_502), U1.E5 (VCCO_DDR_502), U1.G1 (VCCO_DDR_502), U1.H4 (VCCO_DDR_502), U1.L3 (VCCO_DDR_502), U1.P2 (VCCO_DDR_502), U1.R5 (VCCO_DDR_502), U1.U1 (VCCO_DDR_502), U1.V4 (VCCO_DDR_502); also elsewhere on the board
+3V3: C110.1, C111.1, C112.1, C123.1, C130.1, C131.1, C132.1, C133.1, C134.1, C135.1, C136.1, U1.B6 (VCCO_MIO0_500), U1.D7 (VCCO_MIO0_500), U1.K6 (VCCO_0), U1.N6 (RSVDVCC3), U1.N19 (VCCO_34), U1.R6 (RSVDVCC2), U1.R15 (VCCO_34), U1.T6 (RSVDVCC1), U1.T8 (VCCO_13), U1.T18 (VCCO_34), U1.U11 (VCCO_13), U1.V14 (VCCO_34), U1.W7 (VCCO_13), U1.W17 (VCCO_34), U1.Y10 (VCCO_13), U1.Y20 (VCCO_34); also elsewhere on the board
GND: C92.2, C93.2, C94.2, C95.2, C96.2, C97.2, C98.2, C99.2, C100.2, C101.2, C102.2, C103.2, C104.2, C105.2, C106.2, C107.2, C108.2, C109.2, C110.2, C111.2, C112.2, C113.2, C114.2, C115.2, C116.2, C117.2, C118.2, C119.2, C120.2, C121.2, C122.2, C123.2, C124.2, C125.2, C126.2, C127.2, C128.2, C129.2, C130.2, C131.2, C132.2, C133.2, C134.2, C135.2, C136.2, C173.2, U1.A8 (GND), U1.A18 (GND), U1.B1 (GND), U1.B11 (GND), U1.C4 (GND), U1.C9 (GND), U1.C14 (GND), U1.D17 (GND), U1.E10 (GND), U1.E20 (GND), U1.F3 (GND), U1.F7 (GND), U1.F11 (VCCBATT_0), U1.G10 (GND), U1.G12 (GND), U1.G16 (GND), U1.H7 (GND), U1.H9 (GND), U1.H11 (GND), U1.H13 (GND), U1.H19 (GND), U1.J2 (GND), U1.J8 (GND), U1.J10 (GNDADC_0), U1.J12 (GND), U1.K5 (GND), U1.K7 (GND), U1.K9 (VP_0), U1.K10 (VREFN_0), U1.K11 (GND), U1.K13 (GND), U1.K15 (GND), U1.L8 (GND), U1.L9 (VREFP_0), U1.L10 (VN_0), U1.L12 (GND), U1.L18 (GND), U1.M1 (GND), U1.M7 (GND), U1.M9 (DXP_0), U1.M10 (DXN_0), U1.M11 (GND), U1.M13 (GND), U1.N4 (GND), U1.N8 (GND), U1.N10 (GND), U1.N12 (GND), U1.N14 (GND), U1.P7 (GND), U1.P9 (GND), U1.P11 (GND), U1.P13 (GND), U1.P17 (GND), U1.R8 (GND), U1.R12 (GND), U1.R20 (GND), U1.T3 (GND), U1.T7 (GND), U1.T13 (GND), U1.U6 (GND), U1.U16 (GND), U1.V9 (GND), U1.V19 (GND), U1.W2 (GND), U1.W12 (GND), U1.Y5 (GND), U1.Y15 (GND); also elsewhere on the board

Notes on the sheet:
XC7Z010 power pins
VCCPAUX
VCCO_MIO0
Analog
VCCO_0
VCCO_35
VCCO_DDR
VCCINT
VCCO_34
PS Bypass Caps.
VCCAUX
VCCBRAM
PL Bypass Caps.
VCCO_MIO1
VCCPINT
